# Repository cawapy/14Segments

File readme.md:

# Gallery

## Plain PCB

### Front

### Back

## Master Board Assembly

### Front

### Back

## Slave Board Assembly

### Front

### Back

## Master + Slave Configuration

### Front

### Back

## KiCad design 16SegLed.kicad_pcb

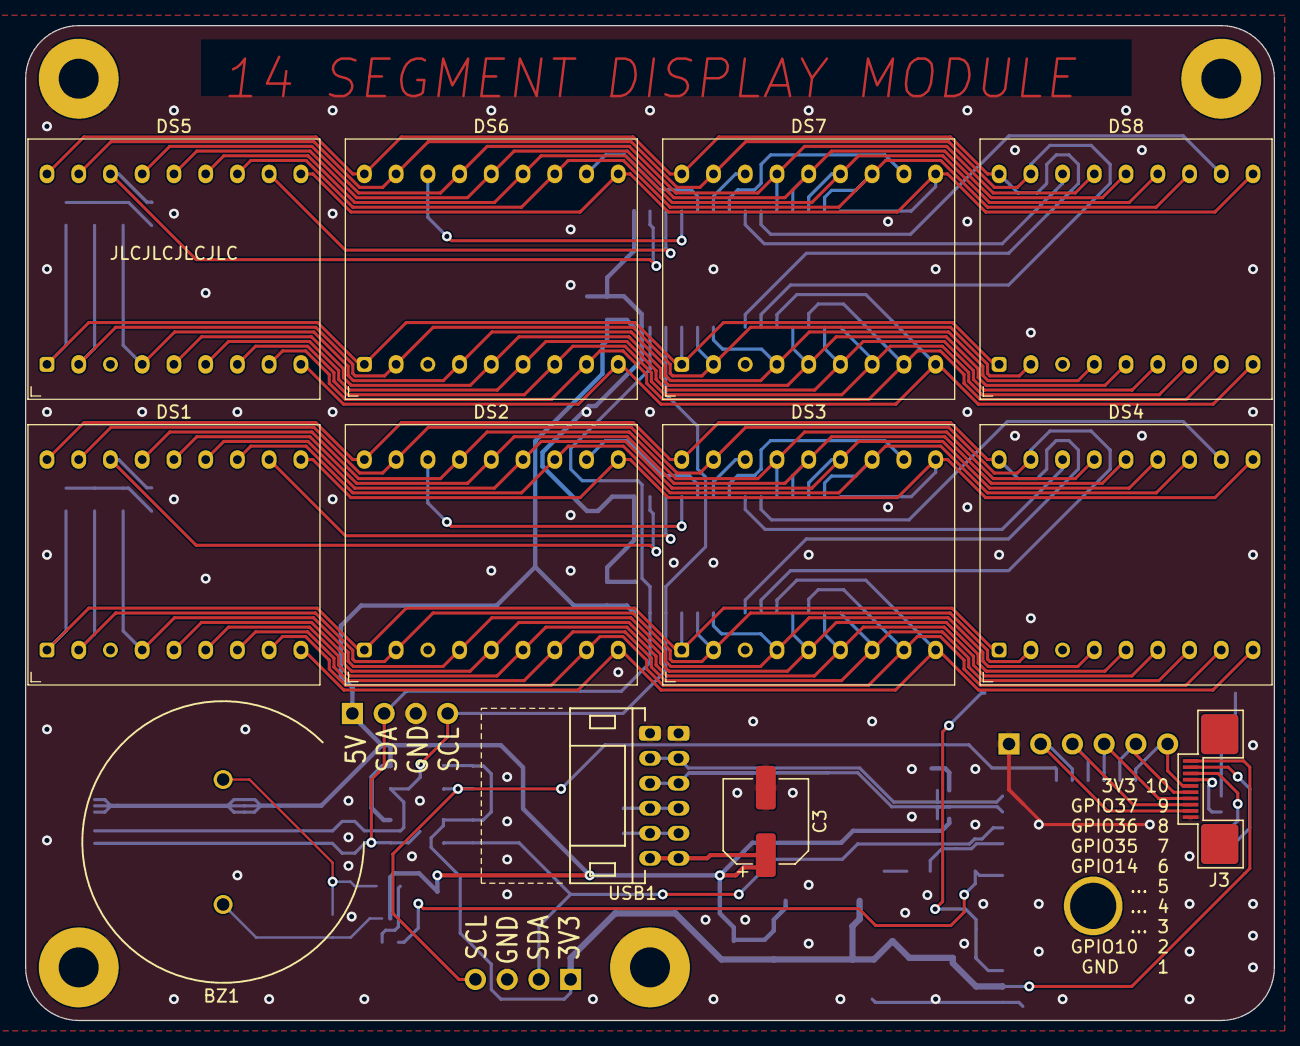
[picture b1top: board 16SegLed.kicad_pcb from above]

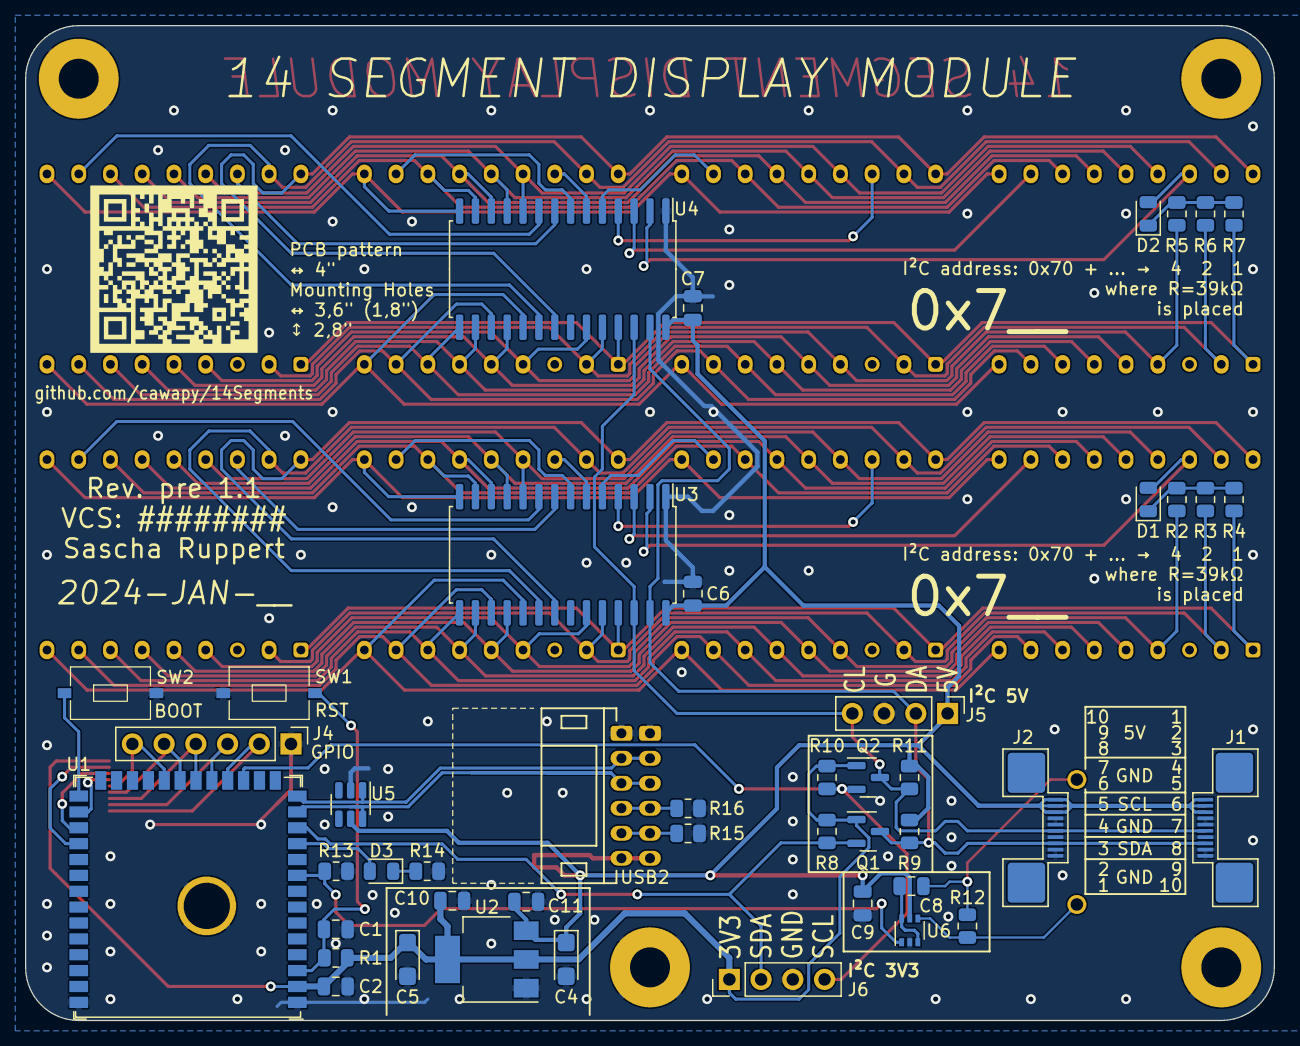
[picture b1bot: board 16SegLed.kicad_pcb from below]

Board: 2 copper layers, 99.9 x 79.6 mm, 62 parts (48 on the bottom side), 75 nets.

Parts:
BZ1: Buzzer; Buzzer-AC2208A
C1, C8, C9: 1µF; C_0805_2012Metric
C2, C6, C7, C10, C11: 100nF; C_0805_2012Metric
C3: 220µF; CP_Elec_6.3x7.7
C4: 10µF; CP_EIA-3216-10_Kemet-I
C5: 100µF; CP_EIA-3216-10_Kemet-I
D1, D2: LIZ Elec CD4148WSP; D_0805_2012Metric
D3: LED; LED_0805_2012Metric
DS1, DS2, DS3, DS4, DS5, DS6, DS7, DS8: 5241AX; DIP-18_600_ELL
FID1: Fiducial; QR-Code
H1, H2, H3, H4: MountingHole; MountingHole_3.2mm_M3_Pad
J1, J2, J3: Conn_01x10; FPC_10
J4: Conn_01x06_Socket; PinHeader_1x06_P2.54mm_Vertical
J5, J6: Conn_01x04_Pin; PinHeader_1x04_P2.54mm_Vertical
Q1, Q2: BSS138; SOT-23
R1, R8, R9, R10, R11, R13: 10kΩ; R_0805_2012Metric
R2, R3, R4, R5, R6, R7: 39kΩ; R_0805_2012Metric
R12: 1M; R_0805_2012Metric
R14: 220Ω; R_0805_2012Metric
R15, R16: 5.1kΩ; R_0805_2012Metric
SW1, SW2: SW_Push; Switch-Order-Ali-2023-12-14
U1: ESP32-S3-WROOM-1; ESP32-S3-WROOM-1U_THT-Pad
U2: AMS1117-3.3; SOT-223-3_TabPin2
U3, U4: HT16K33/28; SOIC-28W_7.5x17.9mm_P1.27mm
U5: SRV05-4; SOT-23-6
U6: 74LVC2G14; SOT-363_SC-70-6
USB1, USB2: HC-PH-6AW-G; PH 1x06 P2.0

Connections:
+3V3: C2.1, C5.1, C10.2, J3.10, J6.1, Q1.1 (G), Q2.1 (G), R1.1, R8.1, R10.1, U1.2 (3V3), U2.2 (VO)
+5V: C3.1, C4.1, C6.1, C7.1, C9.1, C11.2, J1.8, J1.9, J1.10, J2.1, J2.2, J2.3, J5.1, R9.1, R11.1, U2.3 (VI), U3.28 (VDD), U4.28 (VDD), U5.5 (VP), U6.5 (VCC), USB1.6, USB2.6
/BOOT: SW2.1, U1.27 (GPIO0/BOOT)
/BZ+: BZ1.1 (-), R12.1, U6.4
/BZ-: BZ1.2 (+), C8.2, R12.2
/CC1: R15.2, USB1.5, USB2.5
/CC2: R16.1, USB1.4, USB2.4
/CHIP_PU: C1.1, R1.2, SW1.2, U1.3 (EN)
/DisplayGroup0/CFG: D1.1 (K), R2.2, R3.2, R4.2
/DisplayGroup0/COM0: D1.2 (A), DS1.16 (CD1), U3.2 (COM0/AD)
/DisplayGroup0/COM1: DS1.11 (CD2), U3.3 (COM1/KS0)
/DisplayGroup0/COM2: DS2.16 (CD1), U3.4 (COM2/KS1)
/DisplayGroup0/COM3: DS2.11 (CD2), U3.5 (COM3/KS2)
/DisplayGroup0/COM4: DS3.16 (CD1), U3.6 (COM4)
/DisplayGroup0/COM5: DS3.11 (CD2), U3.7 (COM5)
/DisplayGroup0/COM6: DS4.16 (CD1), U3.8 (COM6)
/DisplayGroup0/COM7: DS4.11 (CD2), U3.9 (COM7)
/DisplayGroup0/SEG_{A}: DS1.12 (A), DS2.12 (A), DS3.12 (A), DS4.12 (A), U3.13 (ROW12/K10)
/DisplayGroup0/SEG_{B}: DS1.10 (B), DS2.10 (B), DS3.10 (B), DS4.10 (B), U3.14 (ROW11/K9)
/DisplayGroup0/SEG_{C}: DS1.9 (C), DS2.9 (C), DS3.9 (C), DS4.9 (C), U3.19 (ROW6/K4)
/DisplayGroup0/SEG_{D}: DS1.7 (D), DS2.7 (D), DS3.7 (D), DS4.7 (D), U3.15 (ROW10/K8)
/DisplayGroup0/SEG_{E}: DS1.1 (E), DS2.1 (E), DS3.1 (E), DS4.1 (E), R4.1, U3.25 (ROW0/A2)
/DisplayGroup0/SEG_{F}: DS1.18 (F), DS2.18 (F), DS3.18 (F), DS4.18 (F), U3.21 (ROW4/K2)
/DisplayGroup0/SEG_{G1}: DS1.13 (G1), DS2.13 (G1), DS3.13 (G1), DS4.13 (G1), U3.12 (ROW13/K11)
/DisplayGroup0/SEG_{G2}: DS1.6 (G2), DS2.6 (G2), DS3.6 (G2), DS4.6 (G2), U3.16 (ROW9/K7)
/DisplayGroup0/SEG_{H}: DS1.17 (H), DS2.17 (H), DS3.17 (H), DS4.17 (H), U3.20 (ROW5/K3)
/DisplayGroup0/SEG_{J}: DS1.15 (J), DS2.15 (J), DS3.15 (J), DS4.15 (J), U3.10 (ROW15/K13/INT)
/DisplayGroup0/SEG_{K}: DS1.14 (K), DS2.14 (K), DS3.14 (K), DS4.14 (K), U3.11 (ROW14/K12)
/DisplayGroup0/SEG_{L}: DS1.5 (L), DS2.5 (L), DS3.5 (L), DS4.5 (L), U3.18 (ROW7/K5)
/DisplayGroup0/SEG_{M}: DS1.4 (M), DS2.4 (M), DS3.4 (M), DS4.4 (M), R2.1, U3.23 (ROW2/A0)
/DisplayGroup0/SEG_{N}: DS1.2 (N), DS2.2 (N), DS3.2 (N), DS4.2 (N), R3.1, U3.24 (ROW1/A1)
/DisplayGroup0/SEG_{dp}: DS1.8 (DP), DS2.8 (DP), DS3.8 (DP), DS4.8 (DP), U3.17 (ROW8/K6)
/DisplayGroup1/CFG: D2.1 (K), R5.2, R6.2, R7.2
/DisplayGroup1/COM0: D2.2 (A), DS5.16 (CD1), U4.2 (COM0/AD)
/DisplayGroup1/COM1: DS5.11 (CD2), U4.3 (COM1/KS0)
/DisplayGroup1/COM2: DS6.16 (CD1), U4.4 (COM2/KS1)
/DisplayGroup1/COM3: DS6.11 (CD2), U4.5 (COM3/KS2)
/DisplayGroup1/COM4: DS7.16 (CD1), U4.6 (COM4)
/DisplayGroup1/COM5: DS7.11 (CD2), U4.7 (COM5)
/DisplayGroup1/COM6: DS8.16 (CD1), U4.8 (COM6)
/DisplayGroup1/COM7: DS8.11 (CD2), U4.9 (COM7)
/DisplayGroup1/SEG_{A}: DS5.12 (A), DS6.12 (A), DS7.12 (A), DS8.12 (A), U4.13 (ROW12/K10)
/DisplayGroup1/SEG_{B}: DS5.10 (B), DS6.10 (B), DS7.10 (B), DS8.10 (B), U4.14 (ROW11/K9)
/DisplayGroup1/SEG_{C}: DS5.9 (C), DS6.9 (C), DS7.9 (C), DS8.9 (C), U4.19 (ROW6/K4)
/DisplayGroup1/SEG_{D}: DS5.7 (D), DS6.7 (D), DS7.7 (D), DS8.7 (D), U4.15 (ROW10/K8)
/DisplayGroup1/SEG_{E}: DS5.1 (E), DS6.1 (E), DS7.1 (E), DS8.1 (E), R7.1, U4.25 (ROW0/A2)
/DisplayGroup1/SEG_{F}: DS5.18 (F), DS6.18 (F), DS7.18 (F), DS8.18 (F), U4.21 (ROW4/K2)
/DisplayGroup1/SEG_{G1}: DS5.13 (G1), DS6.13 (G1), DS7.13 (G1), DS8.13 (G1), U4.12 (ROW13/K11)
/DisplayGroup1/SEG_{G2}: DS5.6 (G2), DS6.6 (G2), DS7.6 (G2), DS8.6 (G2), U4.16 (ROW9/K7)
/DisplayGroup1/SEG_{H}: DS5.17 (H), DS6.17 (H), DS7.17 (H), DS8.17 (H), U4.20 (ROW5/K3)
/DisplayGroup1/SEG_{J}: DS5.15 (J), DS6.15 (J), DS7.15 (J), DS8.15 (J), U4.10 (ROW15/K13/INT)
/DisplayGroup1/SEG_{K}: DS5.14 (K), DS6.14 (K), DS7.14 (K), DS8.14 (K), U4.11 (ROW14/K12)
/DisplayGroup1/SEG_{L}: DS5.5 (L), DS6.5 (L), DS7.5 (L), DS8.5 (L), U4.18 (ROW7/K5)
/DisplayGroup1/SEG_{M}: DS5.4 (M), DS6.4 (M), DS7.4 (M), DS8.4 (M), R5.1, U4.23 (ROW2/A0)
/DisplayGroup1/SEG_{N}: DS5.2 (N), DS6.2 (N), DS7.2 (N), DS8.2 (N), R6.1, U4.24 (ROW1/A1)
/DisplayGroup1/SEG_{dp}: DS5.8 (DP), DS6.8 (DP), DS7.8 (DP), DS8.8 (DP), U4.17 (ROW8/K6)
/IO10: J3.2, J4.2, U1.18 (GPIO10/TOUCH10/ADC1_CH9/FSPICS0/FSPIIO4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)
/IO11: J3.3, J4.3, U1.19 (GPIO11/TOUCH11/ADC2_CH0/FSPID/FSPIIO5/S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)
/IO12: J3.4, J4.4, U1.20 (GPIO12/TOUCH12/ADC2_CH1/FSPICLK/FSPIIO6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)
/IO13: J3.5, J4.5, U1.21 (GPIO13/TOUCH13/ADC2_CH2/FSPIQ/FSPIIO7/S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)
/IO14: J3.6, J4.6, U1.22 (GPIO14/TOUCH14/ADC2_CH3/FSPIWP/FSPIDQS/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)
/IO35: J3.7, U1.28 (SPIIO6/GPIO35/FSPID/SUBSPID)
/IO36: J3.8, U1.29 (SPIIO7/GPIO36/FSPICLK/SUBSPICLK)
/IO37: J3.9, U1.30 (SPIDQS/GPIO37/FSPIQ/SUBSPIQ)
/LED: D3.2 (A), U1.11 (GPIO18/U1RXD/ADC2_CH7/CLK_OUT3)
/SCL3V3: J6.4, Q2.2 (S), R10.2, U1.17 (GPIO9/TOUCH9/ADC1_CH8/FSPIHD/SUBSPIHD)
/SCL5V: J1.5, J2.6, J5.4, Q2.3 (D), R11.2, U3.26 (SCL), U4.26 (SCL)
/SDA3V3: J6.2, Q1.2 (S), R8.2, U1.12 (GPIO8/TOUCH8/ADC1_CH7/SUBSPICS1)
/SDA5V: J1.3, J2.8, J5.2, Q1.3 (D), R9.2, U3.27 (SDA), U4.27 (SDA)
/SND: R13.1, U1.9 (GPIO16/U0CTS/ADC2_CH5/XTAL_32K_N), U6.1
/USB_D_MINUS: U1.13 (GPIO19/U1RTS/ADC2_CH8/CLK_OUT2/USB_D-), U5.6 (IO4), USB1.3, USB2.3
/USB_D_PLUS: U1.14 (GPIO20/U1CTS/ADC2_CH9/CLK_OUT1/USB_D+), U5.1 (IO1), USB1.2, USB2.2
/~SND: C8.1, U6.3, U6.6
GND: C1.2, C2.2, C3.2, C4.2, C5.2, C6.2, C7.2, C9.2, C10.1, C11.1, H1.1, H2.1, H3.1, H4.1, J1.1, J1.2, J1.4, J1.6, J1.7, J2.4, J2.5, J2.7, J2.9, J2.10, J3.1, J4.1, J5.3, J6.3, R13.2, R14.2, R15.1, R16.2, SW1.1, SW2.2, U1.1 (GND), U1.40 (GND), U1.41 (GND), U2.1 (GND), U3.1 (VSS), U4.1 (VSS), U5.2 (VN), U6.2 (GND), USB1.1, USB2.1
unnamed: D3.1 (K), R14.1

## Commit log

2024-01-06 Flipped all SMD components to back side
    - Exceptions: large electrolytic capacitor, optional GPIO connector
2024-01-06 Add QR code for repository @ github
2024-01-06 Add teardrops
2024-01-06 Cleanup repo
2024-01-06 Cleaning up Fab layers
2024-01-06 Use meaningful segment net names
2024-01-06 Ignore Kicad lock files
2024-01-06 Rearrange ROW assignment so digits are scanned consecutively from left to right
2024-01-06 Improve routing of power and I2C nets for LED drivers
2024-01-07 Rearrange GND vias
2024-01-07 Connect mounting holes to ground
2024-01-07 Enlarge FPC connector mounting pads to enable hand soldering
2024-01-07 Fix 3.3 V regulator circuit
    - Use polarized footprints for tantalum capacitors
    - Add 100nF at input and output of AMS1117
2024-01-07 Add boxes to component groups on silkscreen
    - including rearrangement of piezo buzzer's discharge resistor closer to other parts of that group
2024-01-07 Rearrange I2C 3V3 testconnector into less crowded area on PCB
2024-01-07 Update USB connectors to be able to move I2C 5V test connector to less crowded place
    - using 2 of them (support installation on front and back in parallel in case needed differently in application than in prototype)
    - using own footprint, matching LCSC part C5342444
    - including own 3d model
2024-01-07 Reset usage of flag "do not place"
2024-01-07 Include teardrops for through-hole pads
2024-01-07 Include readme with some sample pictures
2024-01-07 Include commit hash on PCB for first revision
2024-01-07 Add Gerber files for 1.0
2024-01-14 Add comment on wall/panel mount USB-C socket
2024-01-15 Support native USB-C
    - use 6P terminal for wall mount USB-C socket
    - include 2x 5k1 resistors for CC1 and CC2
    - larger footprints of connectors require partial re-layout
2024-01-22 Create schematic PDF
    - Define and use slim sheet template
    - Define sheet values
    - Rearrange schematics for printout
2024-01-22 Include ibom config file
